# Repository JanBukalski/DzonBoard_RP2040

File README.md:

# DzonBoard

MCU based on RP2040 microcontroller.
Pin Layout is Equal to Raspberry Pi Pico Pin Layout.

# Why devboard

I made it becouse i think it is fun. And i wanted to learn KiCad.

Now i made working PCB. Before i had 40 errors and now i have 0 :)

# Pictures

Pictures are in pics/ folder.

# BOM

BOM is in bom.csv file

# Example software

Example firmware is in examples/ folder..

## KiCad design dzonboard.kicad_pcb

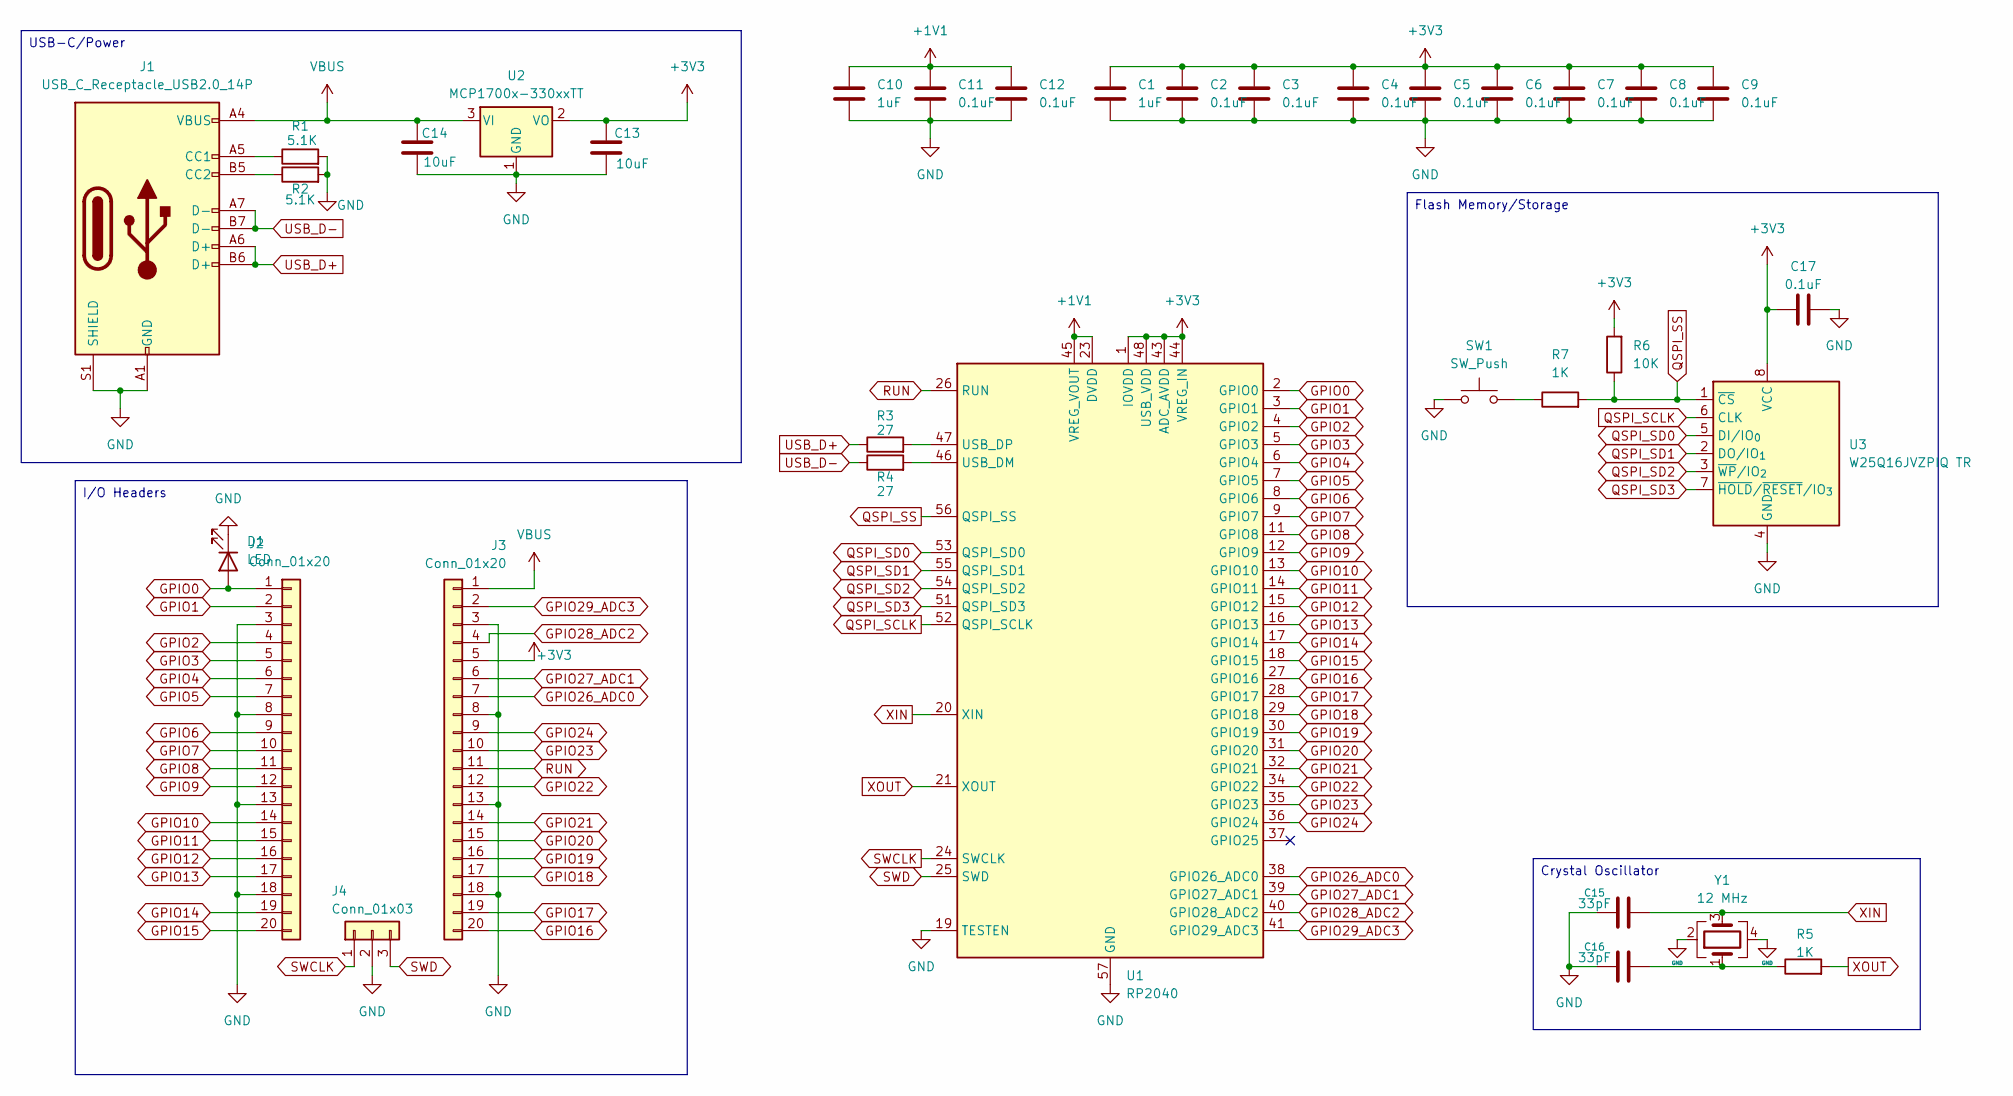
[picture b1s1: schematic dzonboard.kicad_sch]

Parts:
C1, C10: 1uF; C_0402_1005Metric
C2, C3, C4, C5, C6, C7, C8, C9, C11, C12, C17: 0.1uF; C_0402_1005Metric
C13, C14: 10uF; C_0402_1005Metric
C15, C16: 33pF; C_0402_1005Metric
D1: LED; LED_0805_2012Metric
J1: USB_C_Receptacle_USB2.0_14P; USB_C_Receptacle_HRO_TYPE-C-31-M-12
J2, J3: Conn_01x20; PinHeader_1x20_P2.54mm_Vertical
J4: Conn_01x03; PinHeader_1x03_P2.54mm_Vertical
R1, R2: 5.1K; R_0402_1005Metric
R3, R4: 27; R_0402_1005Metric
R5, R7: 1K; R_0402_1005Metric
R6: 10K; R_0402_1005Metric
SW1: SW_Push; SW_Push_SPST_NO_Alps_SKRK
U1: RP2040; QFN-56-1EP_7x7mm_P0.4mm_EP3.2x3.2mm
U2: MCP1700x-330xxTT; SOT-23
U3: W25Q16JVZPIQ TR; Winbond_USON-8-1EP_3x2mm_P0.5mm_EP0.2x1.6mm
Y1: 12 MHz; Crystal_SMD_3225-4Pin_3.2x2.5mm

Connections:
+1V1: C10.1, C11.1, C12.1, U1.23 (DVDD), U1.45 (VREG_VOUT), U1.50 (DVDD)
+3V3: C1.1, C2.1, C3.1, C4.1, C5.1, C6.1, C7.1, C8.1, C9.1, C13.1, C17.1, J3.5, R6.2, U1.1 (IOVDD), U1.10 (IOVDD), U1.22 (IOVDD), U1.33 (IOVDD), U1.42 (IOVDD), U1.43 (ADC_AVDD), U1.44 (VREG_IN), U1.48 (USB_VDD), U1.49 (IOVDD), U2.2 (VO), U3.8 (VCC)
GND: C1.2, C2.2, C3.2, C4.2, C5.2, C6.2, C7.2, C8.2, C9.2, C10.2, C11.2, C12.2, C13.2, C14.2, C15.1, C16.1, C17.2, D1.1 (K), J1.A1 (GND), J1.A12 (GND), J1.B1 (GND), J1.B12 (GND), J1.S1 (SHIELD), J2.3, J2.8, J2.13, J2.18, J3.3, J3.8, J3.13, J3.18, J4.2, R1.2, R2.2, SW1.1, U1.19 (TESTEN), U1.57 (GND), U2.1 (GND), U3.4 (GND), Y1.2, Y1.4
GPIO0: D1.2 (A), J2.1, U1.2 (GPIO0)
GPIO1: J2.2, U1.3 (GPIO1)
GPIO2: J2.4, U1.4 (GPIO2)
GPIO3: J2.5, U1.5 (GPIO3)
GPIO4: J2.6, U1.6 (GPIO4)
GPIO5: J2.7, U1.7 (GPIO5)
GPIO6: J2.9, U1.8 (GPIO6)
GPIO7: J2.10, U1.9 (GPIO7)
GPIO8: J2.11, U1.11 (GPIO8)
GPIO9: J2.12, U1.12 (GPIO9)
GPIO10: J2.14, U1.13 (GPIO10)
GPIO11: J2.15, U1.14 (GPIO11)
GPIO12: J2.16, U1.15 (GPIO12)
GPIO13: J2.17, U1.16 (GPIO13)
GPIO14: J2.19, U1.17 (GPIO14)
GPIO15: J2.20, U1.18 (GPIO15)
GPIO16: J3.20, U1.27 (GPIO16)
GPIO17: J3.19, U1.28 (GPIO17)
GPIO18: J3.17, U1.29 (GPIO18)
GPIO19: J3.16, U1.30 (GPIO19)
GPIO20: J3.15, U1.31 (GPIO20)
GPIO21: J3.14, U1.32 (GPIO21)
GPIO22: J3.12, U1.34 (GPIO22)
GPIO23: J3.10, U1.35 (GPIO23)
GPIO24: J3.9, U1.36 (GPIO24)
GPIO26_ADC0: J3.7, U1.38 (GPIO26_ADC0)
GPIO27_ADC1: J3.6, U1.39 (GPIO27_ADC1)
GPIO28_ADC2: J3.4, U1.40 (GPIO28_ADC2)
GPIO29_ADC3: J3.2, U1.41 (GPIO29_ADC3)
unnamed: C16.2, R5.1, Y1.1
unnamed: J1.A5 (CC1), R1.1
unnamed: J1.B5 (CC2), R2.1
unnamed: R7.1, SW1.2
unnamed: R4.2, U1.46 (USB_DM)
unnamed: R3.2, U1.47 (USB_DP)
QSPI_SCLK: U1.52 (QSPI_SCLK), U3.6 (CLK)
QSPI_SD0: U1.53 (QSPI_SD0), U3.5 (DI/IO_{0})
QSPI_SD1: U1.55 (QSPI_SD1), U3.2 (DO/IO_{1})
QSPI_SD2: U1.54 (QSPI_SD2), U3.3 (~WP/IO_{2})
QSPI_SD3: U1.51 (QSPI_SD3), U3.7 (~HOLD/~RESET/IO_{3})
QSPI_SS: R6.1, R7.2, U1.56 (QSPI_SS), U3.1 (~CS)
RUN: J3.11, U1.26 (RUN)
SWCLK: J4.1, U1.24 (SWCLK)
SWD: J4.3, U1.25 (SWD)
USB_D+: J1.A6 (D+), J1.B6 (D+), R3.1
USB_D-: J1.A7 (D-), J1.B7 (D-), R4.1
VBUS: C14.1, J1.A4 (VBUS), J1.A9 (VBUS), J1.B4 (VBUS), J1.B9 (VBUS), J3.1, U2.3 (VI)
XIN: C15.2, U1.20 (XIN), Y1.3
XOUT: R5.2, U1.21 (XOUT)

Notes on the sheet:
I/O Headers
Flash Memory/Storage
USB-C/Power
Crystal Oscillator

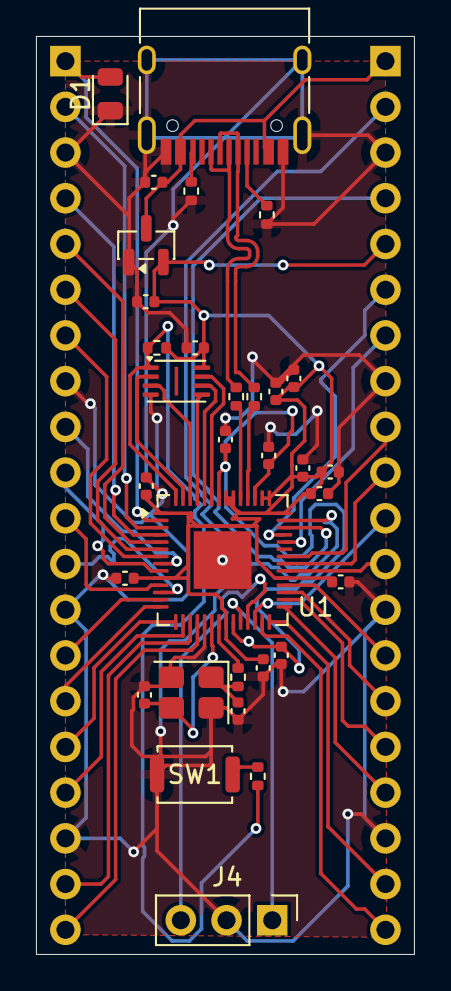
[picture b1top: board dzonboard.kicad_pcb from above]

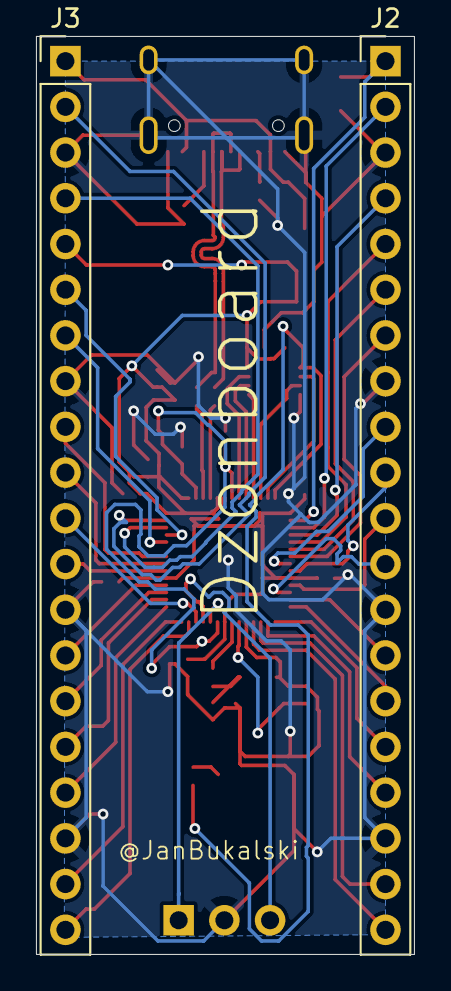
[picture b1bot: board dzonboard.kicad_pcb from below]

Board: 2 copper layers, 21.0 x 51.0 mm, 34 parts (2 on the bottom side), 52 nets.

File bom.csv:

Designator,Footprint,Quantity,Value,LCSC Part #
"C1, C10",0402,2,1uF,
"C11, C12, C17, C2, C3, C4, C5, C6, C7, C8, C9",0402,11,0.1uF,
"C13, C14",0402,2,10uF,
"C15, C16",0402,2,33pF,
D1,0805,1,LED,
J1,USB_C_Receptacle_HRO_TYPE-C-31-M-12,1,USB_C_Receptacle_USB2.0_14P,
"J2, J3",PinHeader_1x20_P2.54mm_Vertical,2,Conn_01x20,
J4,PinHeader_1x03_P2.54mm_Vertical,1,Conn_01x03,
"R1, R2",0402,2,5.1K,
"R3, R4",0402,2,27,
"R5, R7",0402,2,1K,
R6,0402,1,10K,
SW1,SW_Push_SPST_NO_Alps_SKRK,1,SW_Push,
U1,QFN-56-1EP_7x7mm_P0.4mm_EP3.2x3.2mm,1,RP2040,
U2,SOT-23,1,MCP1700x-330xxTT,
U3,Winbond_USON-8-1EP_3x2mm_P0.5mm_EP0.2x1.6mm,1,W25Q16JVZPIQ TR,
Y1,Crystal_SMD_3225-4Pin_3.2x2.5mm,1,12 MHz,

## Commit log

2026-01-04 initial
2026-01-04 readme and others
2026-01-05 updated BOM
2026-01-05 Readme changes
    Added images to the Pictures section in README.
2026-01-05 Update column name from 'Comment' to 'Designation'
2026-01-05 Revise BOM structure and add new fields
    Updated the BOM format to include new columns for Value and LCSC Part #.
2026-01-05 Update bom.csv to include total price and notes
